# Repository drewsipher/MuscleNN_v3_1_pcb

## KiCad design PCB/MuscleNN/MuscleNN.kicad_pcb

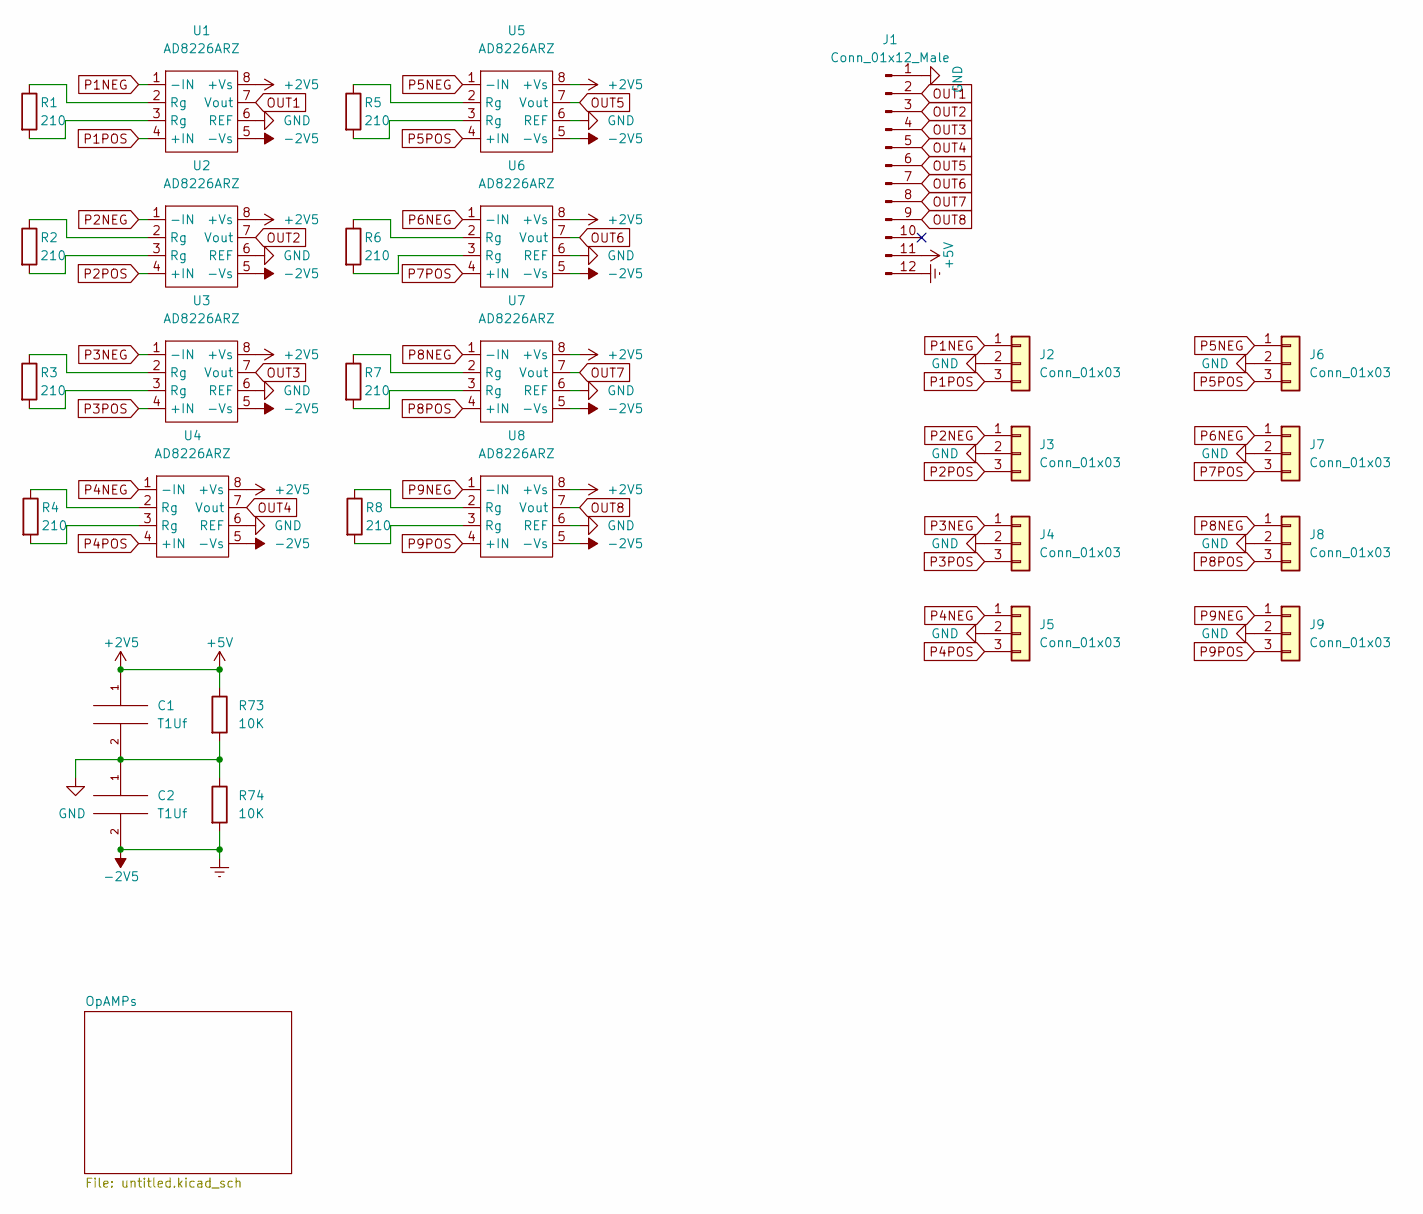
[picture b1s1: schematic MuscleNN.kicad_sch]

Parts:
C1, C2: T1Uf; C_0603_1608Metric_Pad1.08x0.95mm_HandSolder
J1: Conn_01x12_Male; PinHeader_1x12_P2.54mm_Vertical
J2, J3, J4, J5, J6, J7, J8, J9: Conn_01x03; PinHeader_1x03_P2.54mm_Vertical
R1, R2, R3, R4, R5, R6, R7, R8: 210; R_0603_1608Metric_Pad0.98x0.95mm_HandSolder
R73, R74: 10K; R_0603_1608Metric_Pad0.98x0.95mm_HandSolder
U1, U2, U3, U4, U5, U6, U7, U8: AD8226ARZ; SOIC-8_3.9x4.9mm_P1.27mm

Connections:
+2V5: C1.1, J1.11, R73.1, U1.8 (+Vs), U2.8 (+Vs), U3.8 (+Vs), U4.8 (+Vs), U5.8 (+Vs), U6.8 (+Vs), U7.8 (+Vs), U8.8 (+Vs); also elsewhere on the board
-2V5: C2.2, J1.12, R74.2, U1.5 (-Vs), U2.5 (-Vs), U3.5 (-Vs), U4.5 (-Vs), U5.5 (-Vs), U6.5 (-Vs), U7.5 (-Vs), U8.5 (-Vs); also elsewhere on the board
GND: C1.2, C2.1, J1.1, J2.2, J3.2, J4.2, J5.2, J6.2, J7.2, J8.2, J9.2, R73.2, R74.1, U1.6 (REF), U2.6 (REF), U3.6 (REF), U4.6 (REF), U5.6 (REF), U6.6 (REF), U7.6 (REF), U8.6 (REF); also elsewhere on the board
unnamed: R1.1, U1.2 (Rg)
unnamed: R1.2, U1.3 (Rg)
unnamed: R2.1, U2.2 (Rg)
unnamed: R2.2, U2.3 (Rg)
unnamed: R3.1, U3.2 (Rg)
unnamed: R3.2, U3.3 (Rg)
unnamed: R4.1, U4.2 (Rg)
unnamed: R4.2, U4.3 (Rg)
unnamed: R5.1, U5.2 (Rg)
unnamed: R5.2, U5.3 (Rg)
unnamed: R6.1, U6.2 (Rg)
unnamed: R6.2, U6.3 (Rg)
unnamed: R7.1, U7.2 (Rg)
unnamed: R7.2, U7.3 (Rg)
unnamed: R8.1, U8.2 (Rg)
unnamed: R8.2, U8.3 (Rg)
OUT1: J1.2, U1.7 (Vout); also elsewhere on the board
OUT2: J1.3, U2.7 (Vout); also elsewhere on the board
OUT3: J1.4, U3.7 (Vout); also elsewhere on the board
OUT4: J1.5, U4.7 (Vout); also elsewhere on the board
OUT5: J1.6, U5.7 (Vout); also elsewhere on the board
OUT6: J1.7, U6.7 (Vout); also elsewhere on the board
OUT7: J1.8, U7.7 (Vout); also elsewhere on the board
OUT8: J1.9, U8.7 (Vout); also elsewhere on the board
P1NEG: J2.1, U1.1 (-IN)
P1POS: J2.3, U1.4 (+IN)
P2NEG: J3.1, U2.1 (-IN)
P2POS: J3.3, U2.4 (+IN)
P3NEG: J4.1, U3.1 (-IN)
P3POS: J4.3, U3.4 (+IN)
P4NEG: J5.1, U4.1 (-IN)
P4POS: J5.3, U4.4 (+IN)
P5NEG: J6.1, U5.1 (-IN)
P5POS: J6.3, U5.4 (+IN)
P6NEG: J7.1, U6.1 (-IN)
P7POS: J7.3, U6.4 (+IN)
P8NEG: J8.1, U7.1 (-IN)
P8POS: J8.3, U7.4 (+IN)
P9NEG: J9.1, U8.1 (-IN)
P9POS: J9.3, U8.4 (+IN)

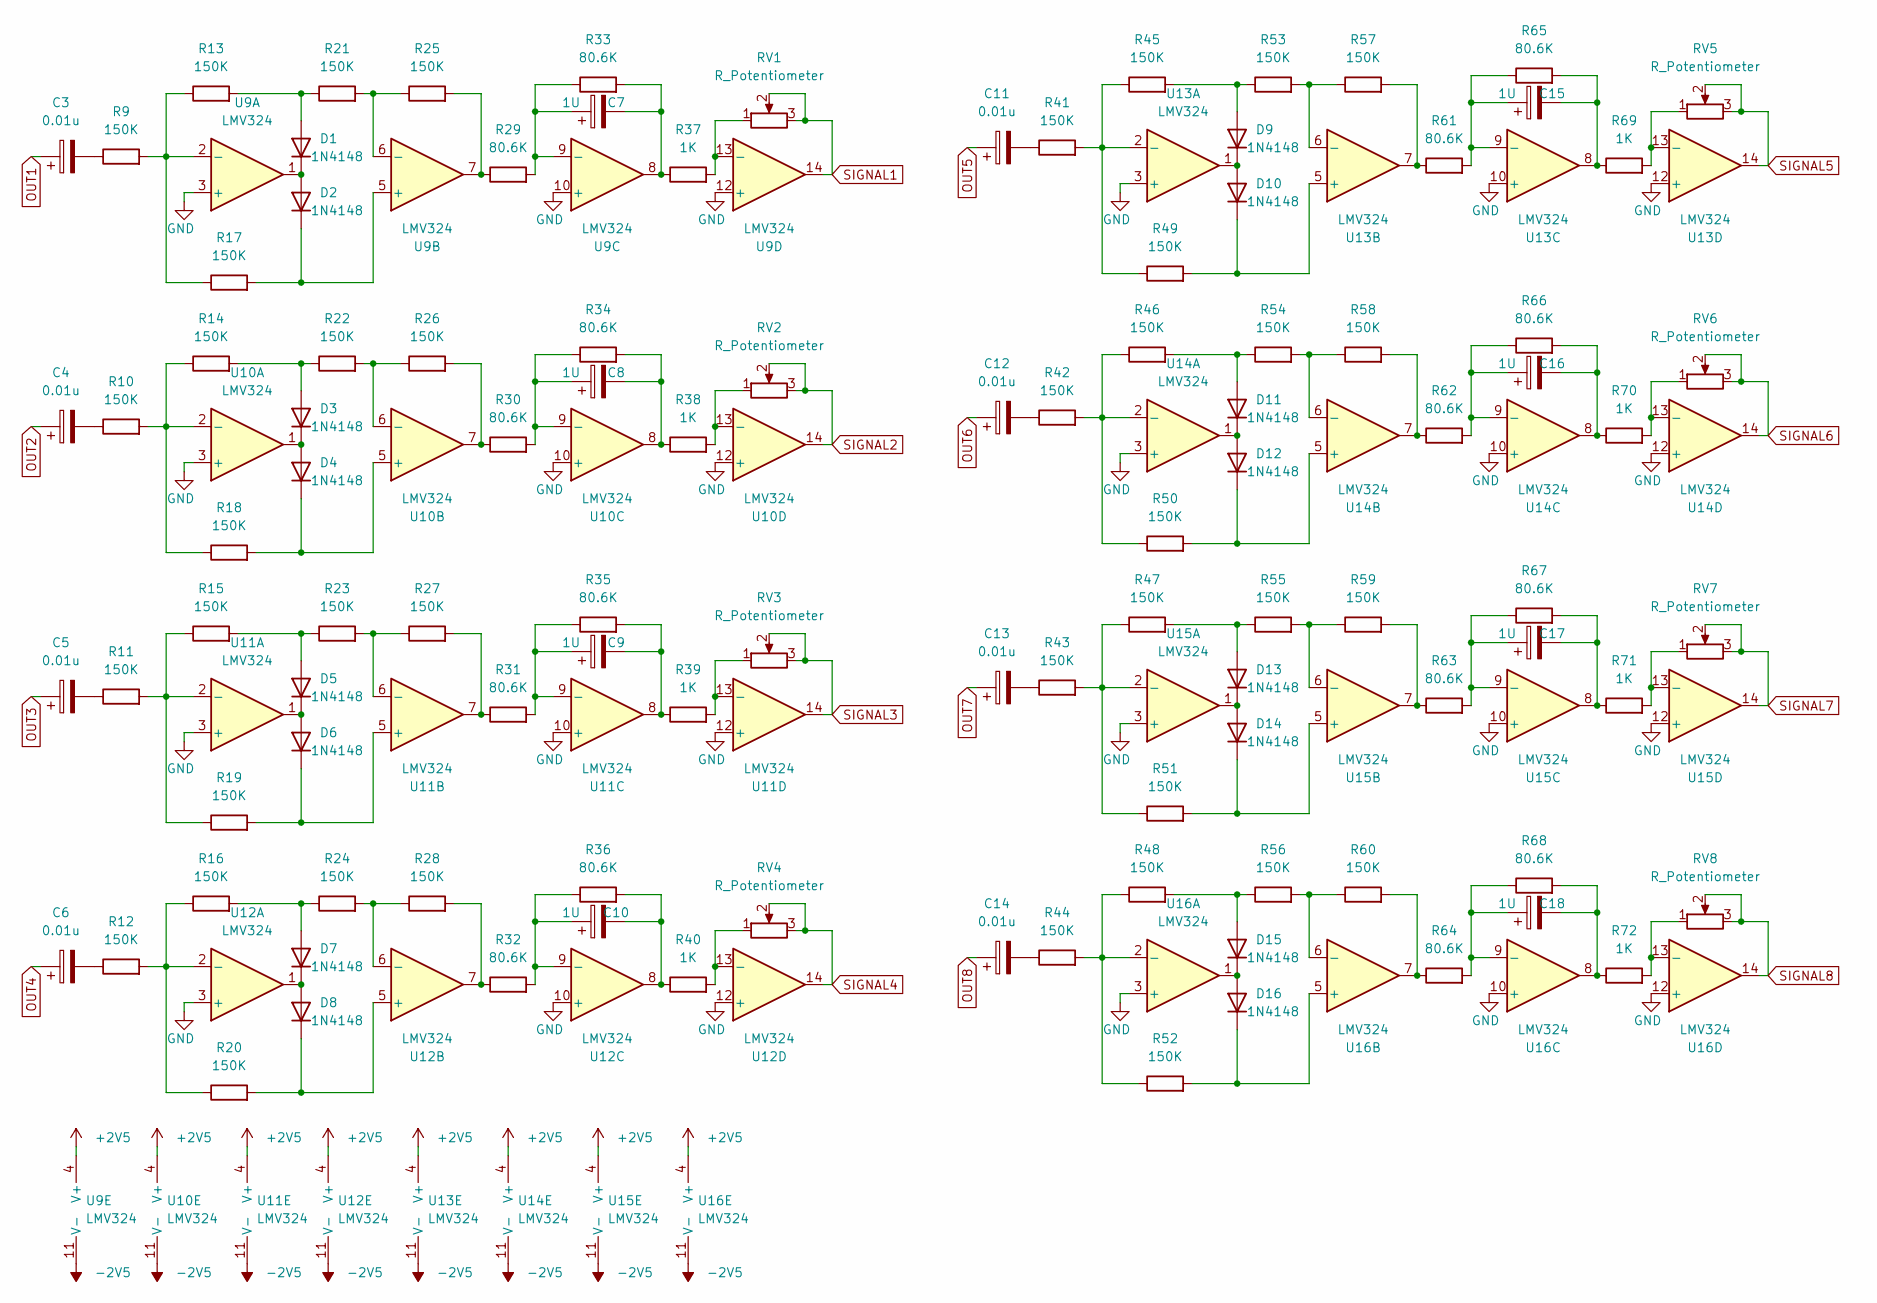
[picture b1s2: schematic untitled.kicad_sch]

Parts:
C3, C4, C5, C6, C11, C12, C13, C14: 0.01u; C_0603_1608Metric_Pad1.08x0.95mm_HandSolder
C7, C8, C9, C10, C15, C16, C17, C18: 1U; C_0603_1608Metric_Pad1.08x0.95mm_HandSolder
D1, D2, D3, D4, D5, D6, D7, D8, D9, D10, D11, D12, D13, D14, D15, D16: 1N4148; D_DO-35_SOD27_P7.62mm_Horizontal
R9, R10, R11, R12, R13, R14, R15, R16, R17, R18, R19, R20, R21, R22, R23, R24, R25, R26, R27, R28, R41, R42, R43, R44, R45, R46, R47, R48, R49, R50, R51, R52, R53, R54, R55, R56, R57, R58, R59, R60: 150K; R_0603_1608Metric
R29, R30, R31, R32, R33, R34, R35, R36, R61, R62, R63, R64, R65, R66, R67, R68: 80.6K; R_0603_1608Metric
R37, R38, R39, R40, R69, R70, R71, R72: 1K; R_0603_1608Metric
RV1, RV2, RV3, RV4, RV5, RV6, RV7, RV8: R_Potentiometer; Potentiometer_Bourns_3314J_Vertical
U9, U10, U11, U13, U15: LMV324
U12, U14, U16: LMV324; SOIC-14_3.9x8.7mm_P1.27mm

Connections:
+2V5: U9.4 (V+), U10.4 (V+), U11.4 (V+), U12.4 (V+), U13.4 (V+), U14.4 (V+), U15.4 (V+), U16.4 (V+); also elsewhere on the board
-2V5: U9.11 (V-), U10.11 (V-), U11.11 (V-), U12.11 (V-), U13.11 (V-), U14.11 (V-), U15.11 (V-), U16.11 (V-); also elsewhere on the board
GND: U9.3 (+), U9.10 (+), U9.12 (+), U10.3 (+), U10.10 (+), U10.12 (+), U11.3 (+), U11.10 (+), U11.12 (+), U12.3 (+), U12.10 (+), U12.12 (+), U13.3 (+), U13.10 (+), U13.12 (+), U14.3 (+), U14.10 (+), U14.12 (+), U15.3 (+), U15.10 (+), U15.12 (+), U16.3 (+), U16.10 (+), U16.12 (+); also elsewhere on the board
unnamed: C3.2, R9.1
unnamed: C4.2, R10.1
unnamed: C7.1, R29.2, R33.1, U9.9 (-)
unnamed: C7.2, R33.2, R37.1, U9.8
unnamed: C8.1, R30.2, R34.1, U10.9 (-)
unnamed: C8.2, R34.2, R38.1, U10.8
unnamed: C9.1, R31.2, R35.1, U11.9 (-)
unnamed: C9.2, R35.2, R39.1, U11.8
unnamed: C10.1, R32.2, R36.1, U12.9 (-)
unnamed: C10.2, R36.2, R40.1, U12.8
unnamed: C11.2, R41.1
unnamed: C12.2, R42.1
unnamed: C15.1, R61.2, R65.1, U13.9 (-)
unnamed: C15.2, R65.2, R69.1, U13.8
unnamed: C16.1, R62.2, R66.1, U14.9 (-)
unnamed: C16.2, R66.2, R70.1, U14.8
unnamed: C17.1, R63.2, R67.1, U15.9 (-)
unnamed: C17.2, R67.2, R71.1, U15.8
unnamed: C18.1, R64.2, R68.1, U16.9 (-)
unnamed: C18.2, R68.2, R72.1, U16.8
unnamed: D1.1 (K), D2.2 (A), U9.1
unnamed: D1.2 (A), R13.2, R21.1
unnamed: D2.1 (K), R17.2, U9.5 (+)
unnamed: D3.1 (K), D4.2 (A), U10.1
unnamed: D3.2 (A), R14.2, R22.1
unnamed: D4.1 (K), R18.2, U10.5 (+)
unnamed: D5.1 (K), D6.2 (A), U11.1
unnamed: D5.2 (A), R15.2, R23.1
unnamed: D6.1 (K), R19.2, U11.5 (+)
unnamed: D7.1 (K), D8.2 (A), U12.1
unnamed: D7.2 (A), R16.2, R24.1
unnamed: D8.1 (K), R20.2, U12.5 (+)
unnamed: D9.2 (A), R45.2, R53.1
unnamed: D10.1 (K), R49.2, U13.5 (+)
unnamed: D9.1 (K), D10.2 (A), U13.1
unnamed: D11.1 (K), D12.2 (A), U14.1
unnamed: D11.2 (A), R46.2, R54.1
unnamed: D12.1 (K), R50.2, U14.5 (+)
unnamed: D13.1 (K), D14.2 (A), U15.1
unnamed: D13.2 (A), R47.2, R55.1
unnamed: D14.1 (K), R51.2, U15.5 (+)
unnamed: D15.1 (K), D16.2 (A), U16.1
unnamed: D15.2 (A), R48.2, R56.1
unnamed: D16.1 (K), R52.2, U16.5 (+)
unnamed: R10.2, R14.1, R18.1, U10.2 (-)
unnamed: C5.2, R11.1
unnamed: R11.2, R15.1, R19.1, U11.2 (-)
unnamed: C6.2, R12.1
unnamed: R12.2, R16.1, R20.1, U12.2 (-)
unnamed: R9.2, R13.1, R17.1, U9.2 (-)
unnamed: R21.2, R25.1, U9.6 (-)
unnamed: R22.2, R26.1, U10.6 (-)
unnamed: R23.2, R27.1, U11.6 (-)
unnamed: R24.2, R28.1, U12.6 (-)
unnamed: R25.2, R29.1, U9.7
unnamed: R26.2, R30.1, U10.7
unnamed: R27.2, R31.1, U11.7
unnamed: R28.2, R32.1, U12.7
unnamed: R37.2, RV1.1, U9.13 (-)
unnamed: R38.2, RV2.1, U10.13 (-)
unnamed: R39.2, RV3.1, U11.13 (-)
unnamed: R40.2, RV4.1, U12.13 (-)
unnamed: R41.2, R45.1, R49.1, U13.2 (-)
unnamed: R42.2, R46.1, R50.1, U14.2 (-)
unnamed: C13.2, R43.1
unnamed: R43.2, R47.1, R51.1, U15.2 (-)
unnamed: C14.2, R44.1
unnamed: R44.2, R48.1, R52.1, U16.2 (-)
unnamed: R53.2, R57.1, U13.6 (-)
unnamed: R54.2, R58.1, U14.6 (-)
unnamed: R55.2, R59.1, U15.6 (-)
unnamed: R56.2, R60.1, U16.6 (-)
unnamed: R57.2, R61.1, U13.7
unnamed: R58.2, R62.1, U14.7
unnamed: R59.2, R63.1, U15.7
unnamed: R60.2, R64.1, U16.7
unnamed: R69.2, RV5.1, U13.13 (-)
unnamed: R70.2, RV6.1, U14.13 (-)
unnamed: R71.2, RV7.1, U15.13 (-)
unnamed: R72.2, RV8.1, U16.13 (-)
OUT1: C3.1; also elsewhere on the board
OUT2: C4.1; also elsewhere on the board
OUT3: C5.1; also elsewhere on the board
OUT4: C6.1; also elsewhere on the board
OUT5: C11.1; also elsewhere on the board
OUT6: C12.1; also elsewhere on the board
OUT7: C13.1; also elsewhere on the board
OUT8: C14.1; also elsewhere on the board
SIGNAL1: RV1.2, RV1.3, U9.14
SIGNAL2: RV2.2, RV2.3, U10.14
SIGNAL3: RV3.2, RV3.3, U11.14
SIGNAL4: RV4.2, RV4.3, U12.14
SIGNAL5: RV5.2, RV5.3, U13.14
SIGNAL6: RV6.2, RV6.3, U14.14
SIGNAL7: RV7.2, RV7.3, U15.14
SIGNAL8: RV8.2, RV8.3, U16.14

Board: 2 copper layers, 141 parts (0 on the bottom side), 131 nets, no tracks yet.

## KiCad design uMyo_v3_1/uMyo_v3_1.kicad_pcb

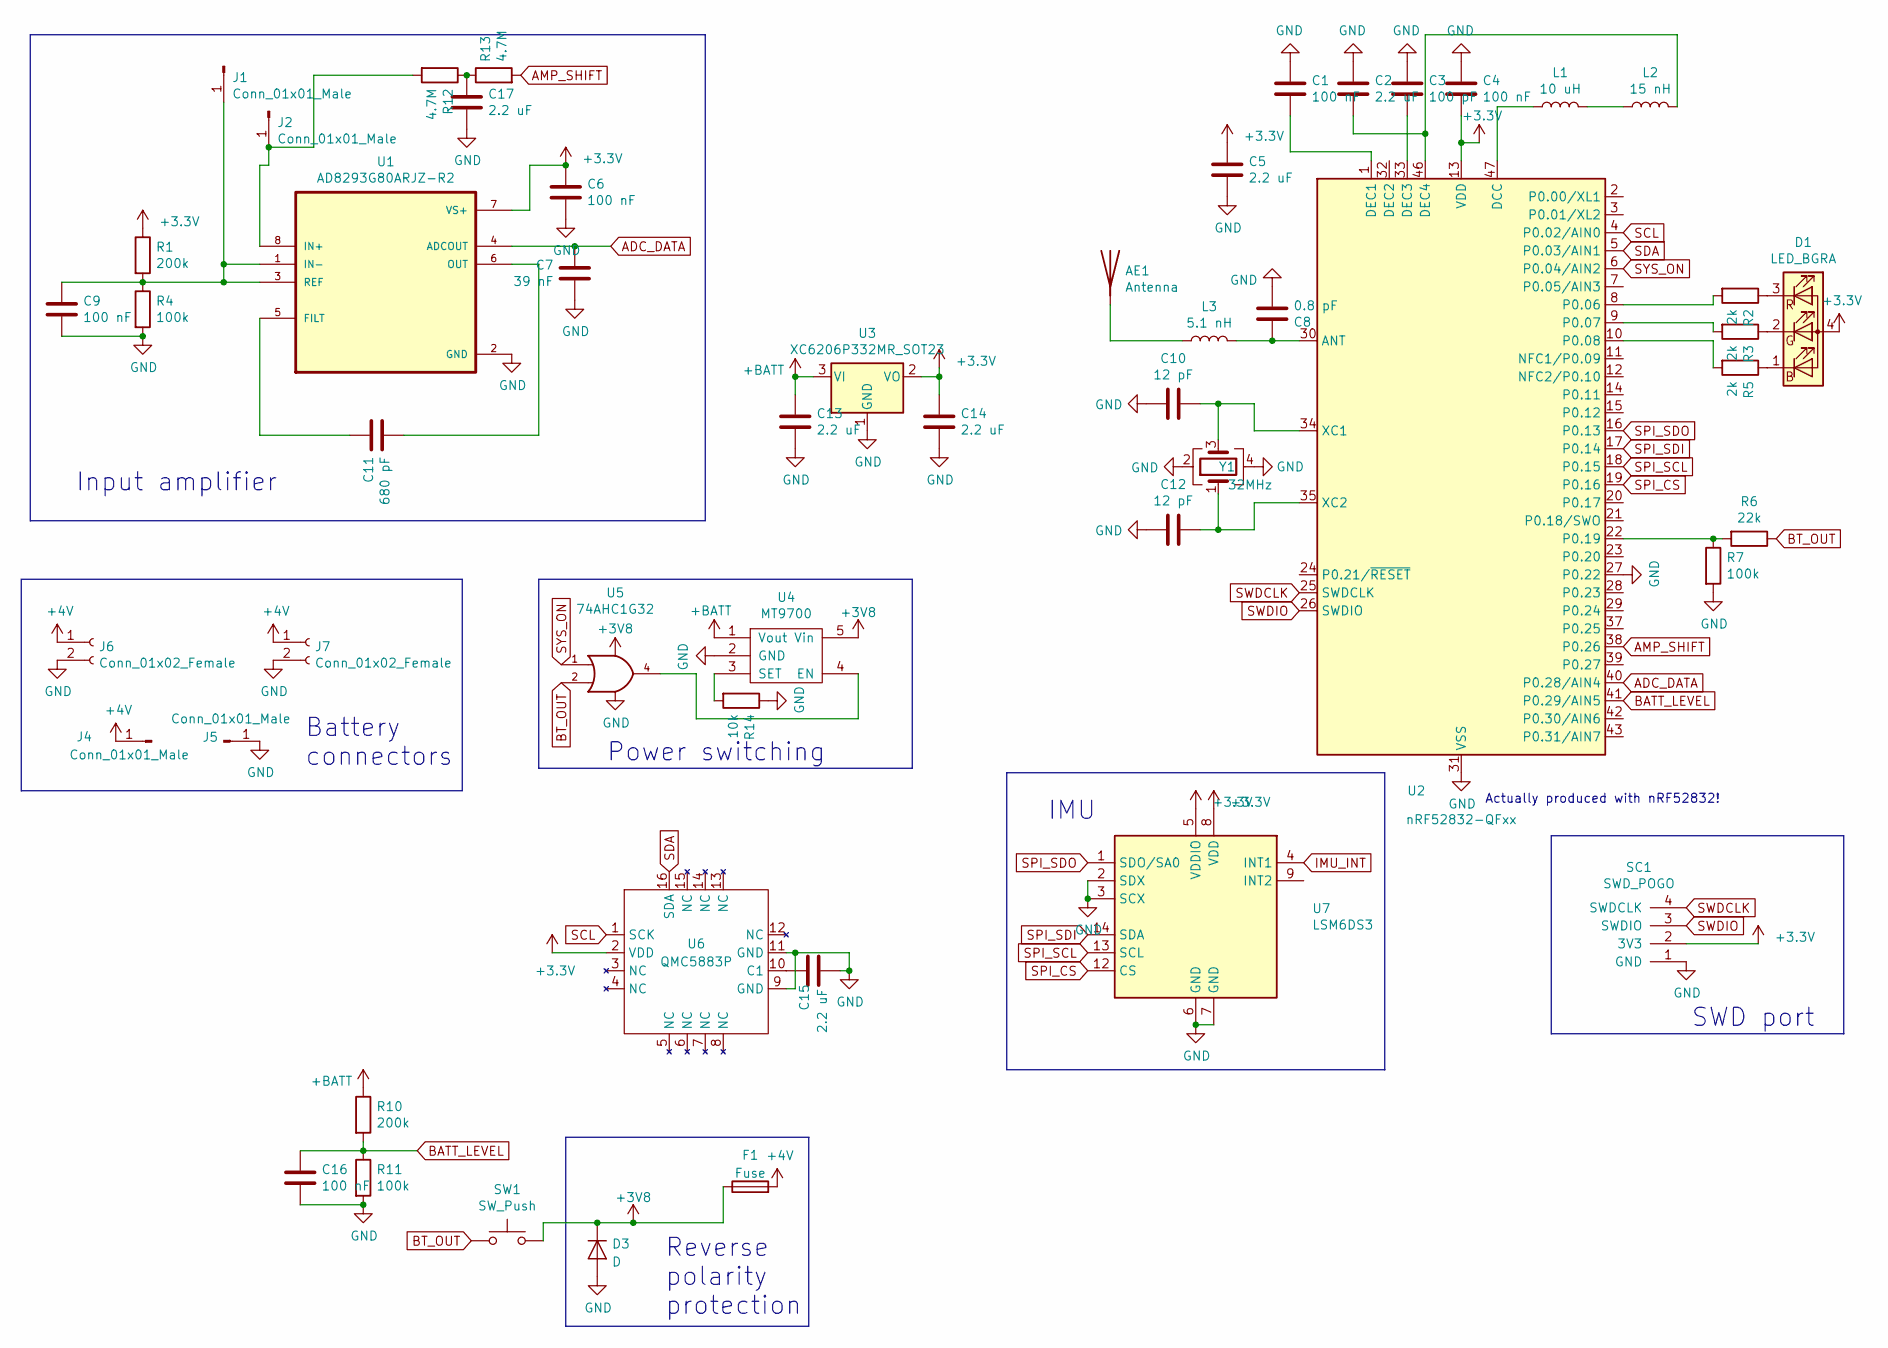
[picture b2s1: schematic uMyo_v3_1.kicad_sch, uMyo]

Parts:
AE1: Antenna; KH3216-A55; JLCPN C484541
C1, C4, C6, C9, C16: 100 nF; C_0402_1005Metric; JLCPN C1525
C2, C5, C13, C14, C15, C17: 2.2 uF; C_0402_1005Metric; JLCPN C12530
C3: 100 pF; C_0402_1005Metric; JLCPN C1546
C7: 39 nF; C_0402_1005Metric; JLCPN C117753
C8: 0.8 pF; C_0402_1005Metric; JLCPN C88902
C10, C12: 12 pF; C_0402_1005Metric; JLCPN C1547
C11: 680 pF; C_0402_1005Metric; JLCPN C113781
D1: LED_BGRA; LED_RGB_0603_a4; JLCPN C282128
D3: D; D_SOD-323; JLCPN C191023
F1: Fuse; Fuse_0603_1608Metric; JLCPN C207011
J1, J2: Conn_01x01_Male; uMyo_dry_connector
J4, J5: Conn_01x01_Male; conn_16_20
J6, J7: Conn_01x02_Female; JST_PH_S2B-PH-SM4-TB_1x02-1MP_P2.00mm_Horizontal; JLCPN C520130
L1: 10 uH; L_0603_1608Metric; JLCPN C1035
L2: 15 nH; L_0402_1005Metric; JLCPN C27143
L3: 5.1 nH; L_0402_1005Metric; JLCPN C86066
R1, R10: 200k; R_0402_1005Metric; JLCPN C25764
R2, R3, R5: 2k; R_0402_1005Metric; JLCPN C4109
R4, R7, R11: 100k; R_0402_1005Metric; JLCPN C25741
R6: 22k; R_0402_1005Metric; JLCPN C25768
R12, R13: 4.7M; R_0402_1005Metric; JLCPN C227116
R14: 10k; R_0402_1005Metric; JLCPN C25744
SC1: SWD_POGO
SW1: SW_Push; SW_SPST_CK_RS282G05A3; JLCPN C2845294
U1: AD8293G80ARJZ-R2; SOT-23-8; JLCPN C141950
U2: nRF52832-QFxx; QFN-48-1EP_6x6mm_Pitch0.4mm; JLCPN C141828
U3: XC6206P332MR_SOT23; SOT-23; JLCPN C5446
U4: MT9700; SOT-23-5; JLCPN C89855
U5: 74AHC1G32; SOT-23-5; JLCPN C507209
U6: QMC5883P; LGA-16_3x3mm_P0.5mm
U7: LSM6DS3; LGA-14_3x2.5mm_P0.5mm_LayoutBorder3x4y; JLCPN C967633
Y1: 32MHz; Crystal_SMD_2016-4Pin_2.0x1.6mm; JLCPN C843260

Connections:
+3V3: C4.1, C5.2, C6.2, C14.2, D1.4 (A), R1.1, SC1.2 (3V3), U1.7 (VS+), U2.13 (VDD), U2.36 (VDD), U2.48 (VDD), U3.2 (VO), U6.2 (VDD), U7.5 (VDDIO), U7.8 (VDD)
+3V8: D3.1 (K), F1.1, SW1.2, U4.5 (Vin), U5.5 (VCC)
+4V: F1.2, J4.1, J6.1, J7.1
+BATT: C13.2, R10.1, U3.3 (VI), U4.1 (Vout)
ADC_DATA: C7.1, U1.4 (ADCOUT), U2.40 (P0.28/AIN4)
AMP_SHIFT: R13.2, U2.38 (P0.26)
BATT_LEVEL: C16.2, R10.2, R11.1, U2.41 (P0.29/AIN5)
BT_OUT: R6.1, SW1.1, U5.2
GND: C1.2, C2.2, C3.2, C4.2, C5.1, C6.1, C7.2, C8.2, C9.1, C10.1, C12.1, C13.1, C14.1, C15.1, C16.1, C17.1, D3.2 (A), J5.1, J6.2, J7.2, R4.2, R7.2, R11.2, R14.1, SC1.1 (GND), U1.2 (GND), U2.27 (P0.22), U2.31 (VSS), U2.45 (VSS), U2.49 (VSS), U3.1 (GND), U4.2 (GND), U5.3 (GND), U6.9 (GND), U6.11 (GND), U7.2 (SDX), U7.3 (SCX), U7.6 (GND), U7.7 (GND), Y1.2, Y1.4
IMU_INT: U7.4 (INT1)
unnamed: AE1.1 (A), L3.1
unnamed: C1.1, U2.1 (DEC1)
unnamed: C2.1, L2.2, U2.46 (DEC4)
unnamed: C3.1, U2.33 (DEC3)
unnamed: C8.1, L3.2, U2.30 (ANT)
unnamed: C9.2, J1.1, R1.2, R4.1, U1.1 (IN-), U1.3 (REF)
unnamed: C10.2, U2.34 (XC1), Y1.3
unnamed: C11.1, U1.5 (FILT)
unnamed: C11.2, U1.6 (OUT)
unnamed: C12.2, U2.35 (XC2), Y1.1
unnamed: C15.2, U6.10 (C1)
unnamed: C17.2, R12.1, R13.1
unnamed: D1.1 (BK), R5.1
unnamed: D1.2 (GK), R3.1
unnamed: D1.3 (RK), R2.1
unnamed: J2.1, R12.2, U1.8 (IN+)
unnamed: L1.1, U2.47 (DCC)
unnamed: L1.2, L2.1
unnamed: R2.2, U2.8 (P0.06)
unnamed: R3.2, U2.9 (P0.07)
unnamed: R5.2, U2.10 (P0.08)
unnamed: R6.2, R7.1, U2.22 (P0.19)
unnamed: R14.2, U4.3 (SET)
unnamed: U4.4 (EN), U5.4
SCL: U2.4 (P0.02/AIN0), U6.1 (SCK)
SDA: U2.5 (P0.03/AIN1), U6.16 (SDA)
SPI_CS: U2.19 (P0.16), U7.12 (CS)
SPI_SCL: U2.18 (P0.15), U7.13 (SCL)
SPI_SDI: U2.17 (P0.14), U7.14 (SDA)
SPI_SDO: U2.16 (P0.13), U7.1 (SDO/SA0)
SWDCLK: SC1.4 (SWDCLK), U2.25 (SWDCLK)
SWDIO: SC1.3 (SWDIO), U2.26 (SWDIO)
SYS_ON: U2.6 (P0.04/AIN2), U5.1

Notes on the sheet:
SWD port
Power switching
Battery connectors
IMU
Reverse polarity protection
Actually produced with nRF52832!
Input amplifier

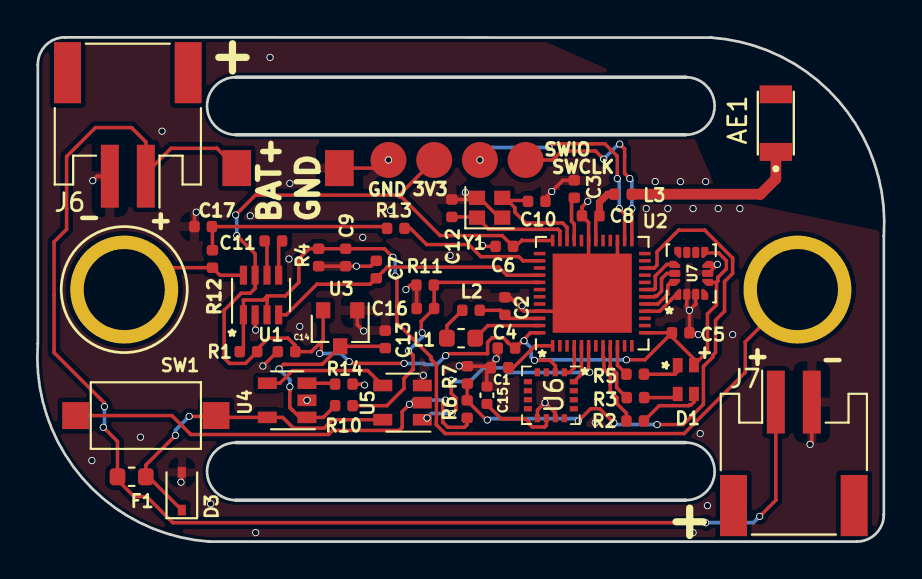
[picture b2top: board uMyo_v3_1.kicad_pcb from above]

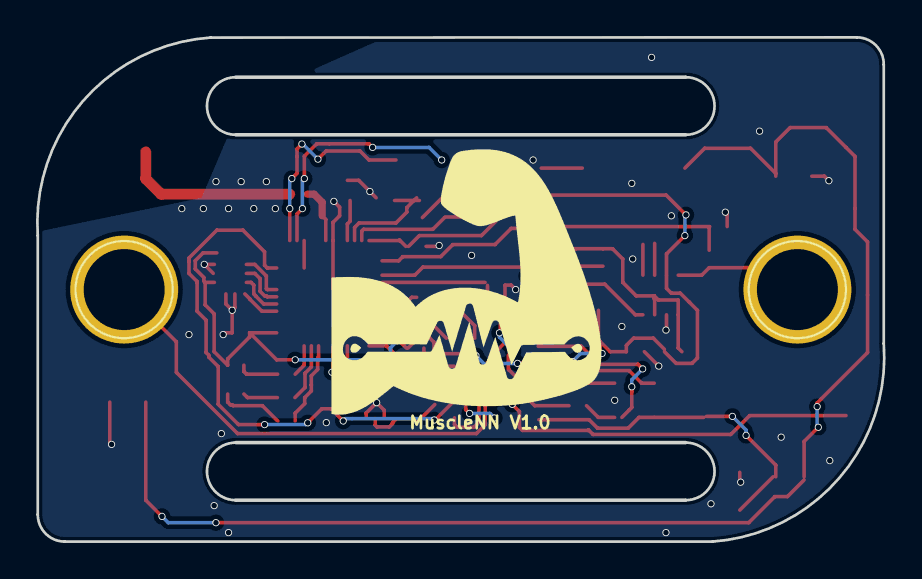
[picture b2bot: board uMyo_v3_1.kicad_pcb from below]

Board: 2 copper layers, 47.0 x 28.0 mm, 52 parts (2 on the bottom side), 42 nets.

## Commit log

2025-04-02 Adding kicad gitignore
2025-04-02 Update to the project to include available and modern parts
2025-04-02 Update Name to MuscleNN
2025-04-02 Added some references and images
2025-04-02 Updated colors
2025-04-11 Added i2c accelerometer to datasheets
